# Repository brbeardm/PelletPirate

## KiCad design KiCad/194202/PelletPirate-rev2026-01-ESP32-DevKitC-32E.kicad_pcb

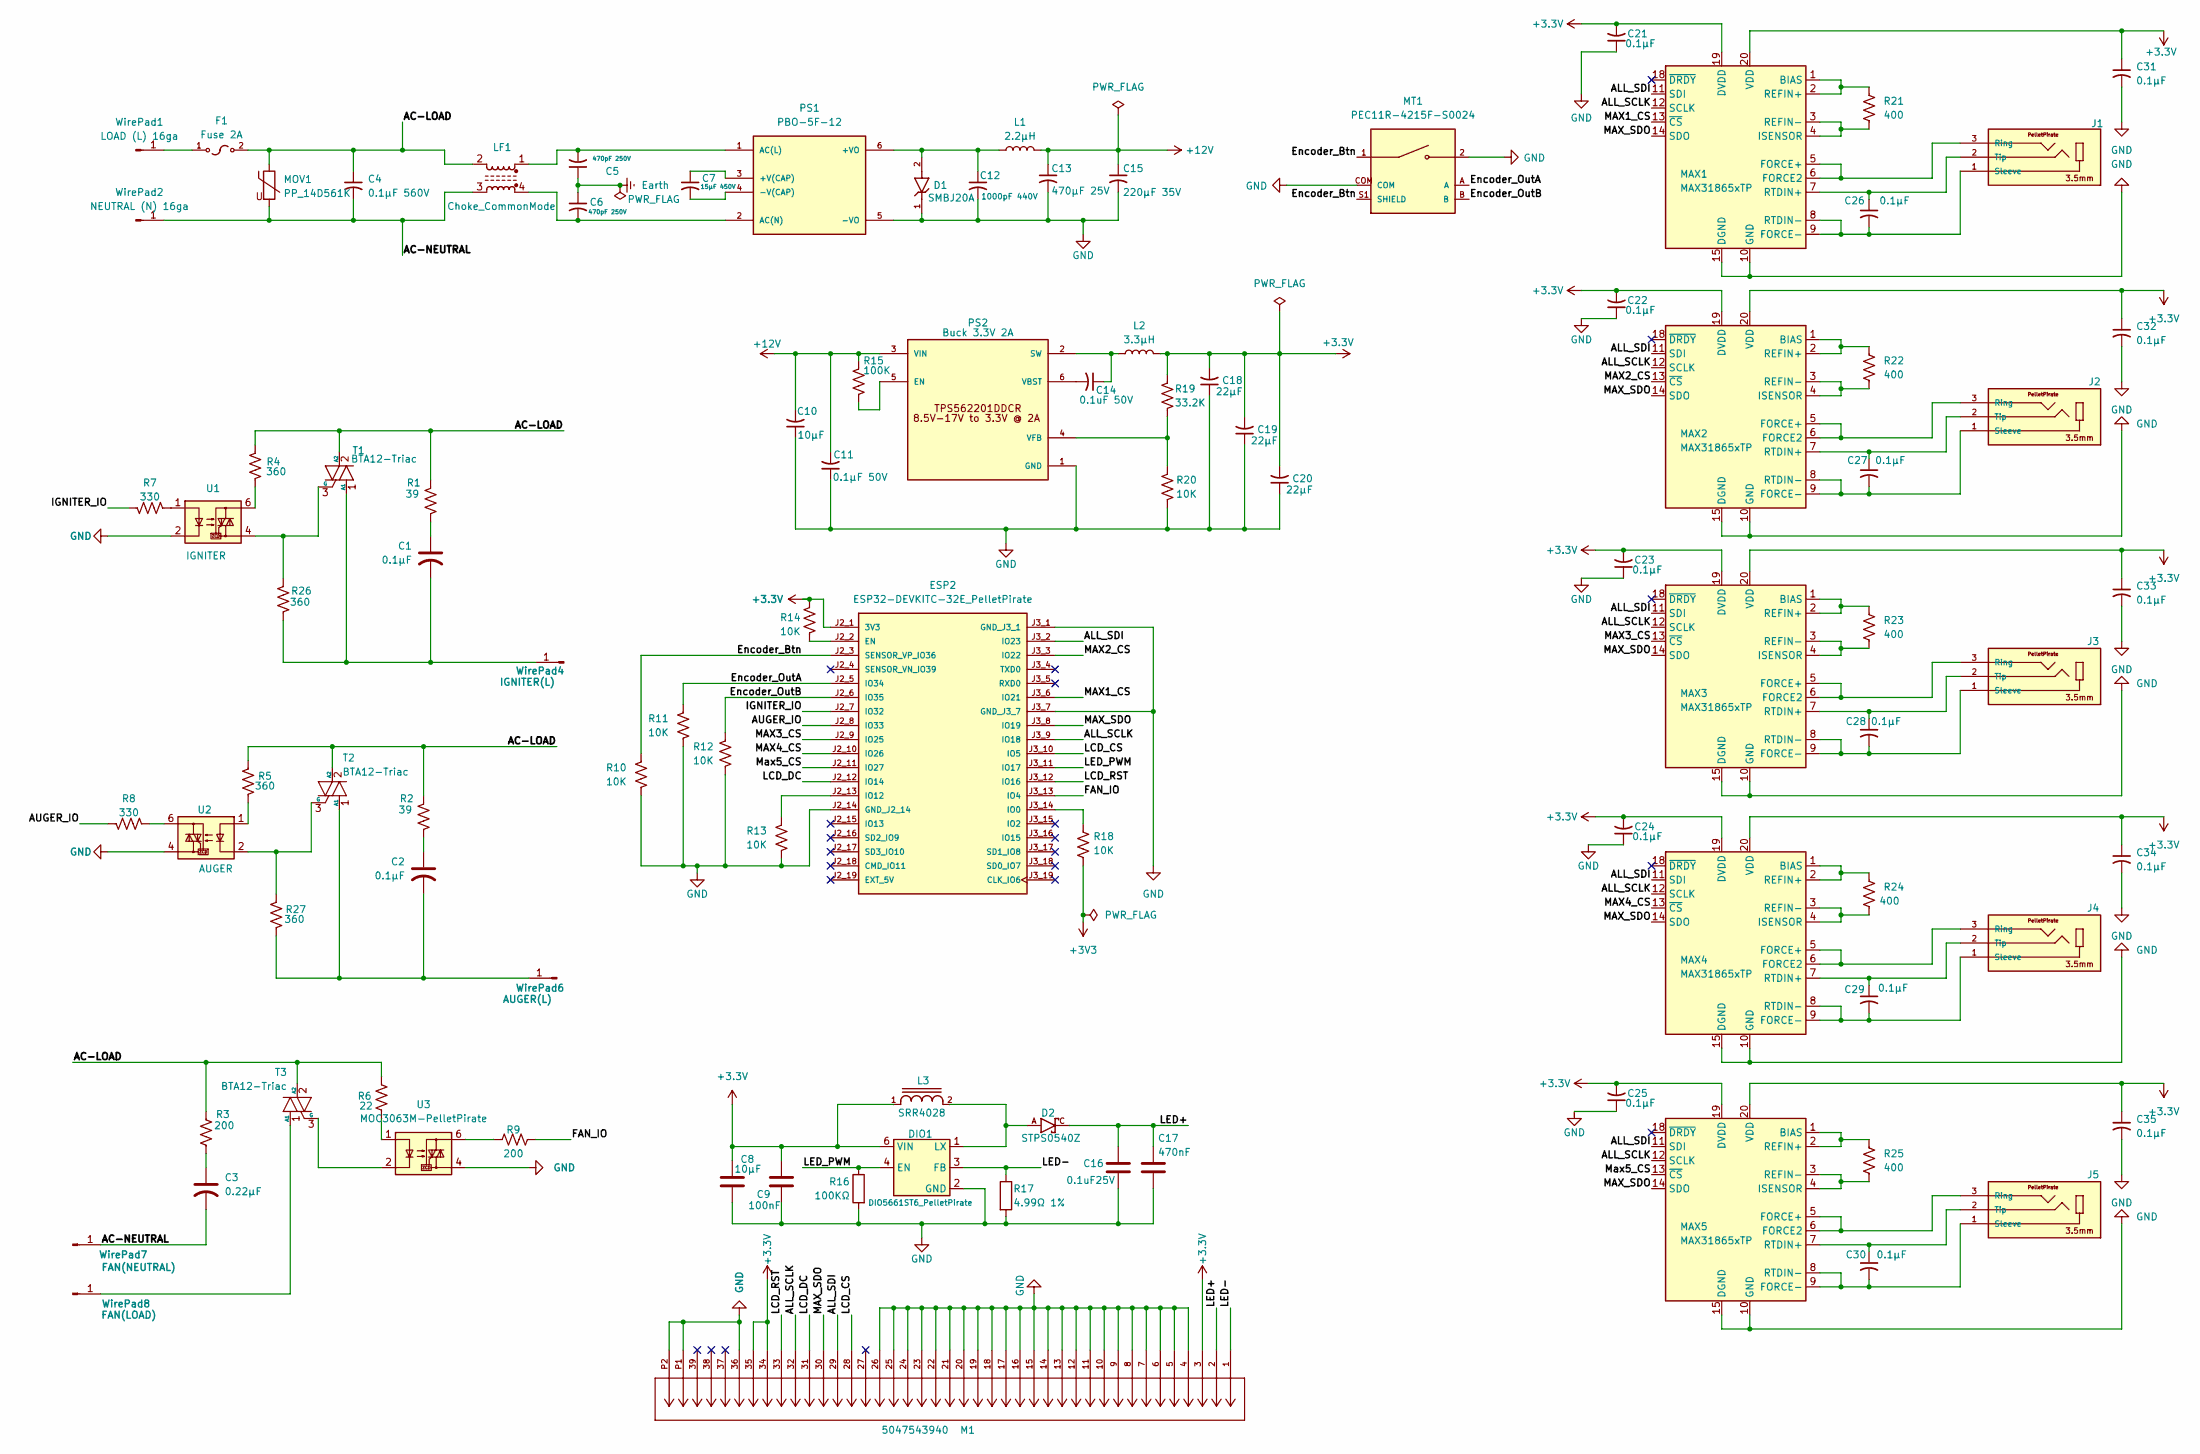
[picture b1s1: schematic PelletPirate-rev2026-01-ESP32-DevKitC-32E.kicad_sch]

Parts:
C1, C2, C21, C22, C23, C24, C25, C26, C27, C28, C29, C30, C31, C32, C33, C34, C35: 0.1µF; C_0805_2012Metric_Pad1.18x1.45mm_HandSolder
C3: 0.22µF; C_0805_2012Metric_Pad1.18x1.45mm_HandSolder
C4: 0.1µF 560V; CAPRR1500W80L1800T500H1050
C5, C6: 470pF 250V; C_Disc_D7.5mm_W5.0mm_P7.50mm
C7: 15µF 450V; CP_Radial_D10.0mm_P5.00mm
C8: 10µF; C_0603_1608Metric_Pad1.08x0.95mm_HandSolder
C9: 100nF; C_0603_1608Metric_Pad1.08x0.95mm_HandSolder
C10: 10µF; C_1206_3216Metric_Pad1.33x1.80mm_HandSolder
C11: 0.1µF 50V; C_0805_2012Metric_Pad1.18x1.45mm_HandSolder
C12: 1000pF 440V; C_Disc_D7.5mm_W5.0mm_P7.50mm
C13: 470µF 25V; CP_Radial_D10.0mm_P5.00mm
C14: 0.1uF 50V; C_0805_2012Metric_Pad1.18x1.45mm_HandSolder
C15: 220µF 35V; CP_Radial_D8.0mm_P3.50mm
C16: 0.1uF25V; C_0805_2012Metric_Pad1.18x1.45mm_HandSolder
C17: 470nF; C_0805_2012Metric_Pad1.18x1.45mm_HandSolder
C18, C19, C20: 22µF; C_1206_3216Metric_Pad1.33x1.80mm_HandSolder
D1: SMBJ20A; DIOM5436X261N_PelletPirate; PARTREV JC.07/04/25 v4; DigiKey_Part_Number SMBJ20ALFCT-ND
D2: STPS0540Z; SOD-123
DIO1: DIO5661ST6_PelletPirate; SOT-23-6
ESP2: ESP32-DEVKITC-32E_PelletPirate; MODULE_ESP32-DEVKITC-32E_PelletPirate; PARTREV 1.4
F1: Fuse 2A; SCHURTER_0031.8201; DigiKey_Part_Number 486-1258-ND
J1, J2, J3, J4, J5: SJ1-3523NG_Jack_PP; CUI_SJ1-3523NG_PelletPirate; PARTREV 1.01
L1: 2.2µH; L_2512_6332Metric
L2: 3.3µH; L_2512_6332Metric
L3: SRR4028
LF1: Choke_CommonMode; Kemet_Choke_SSRH7H_M05408
M1: 5047543940; CON_5047543940_MOL; MANUFACTURER_PART_NUMBER 5047543940
MAX1, MAX2, MAX3, MAX4, MAX5: MAX31865xTP; TQFN-20-1EP_5x5mm_P0.65mm_EP3.25x3.25mm
MOV1: PP_14D561K; Varistor_14mm_p7.5mm
MT1: PEC11R-4215F-S0024; XDCR_PEC11R-4215F-S0024; PARTREV Rev. 09/19; DigiKey_Part_Number PEC11R-4215F-S0024-ND
PS1: PBO-5F-12; PBO-5F-12_pp2; PARTREV 1.0
PS2: Buck 3.3V 2A; SOT95P280X110-6N; PARTREV A
R1, R2: 39; C_0805_2012Metric_Pad1.18x1.45mm_HandSolder
R3, R9: 200; C_0805_2012Metric_Pad1.18x1.45mm_HandSolder
R4, R5, R26, R27: 360; C_0805_2012Metric_Pad1.18x1.45mm_HandSolder
R6: 22; C_0805_2012Metric_Pad1.18x1.45mm_HandSolder
R7, R8: 330; C_0805_2012Metric_Pad1.18x1.45mm_HandSolder
R10, R11, R12, R13, R14, R18, R20: 10K; C_0805_2012Metric_Pad1.18x1.45mm_HandSolder
R15: 100K; C_0805_2012Metric_Pad1.18x1.45mm_HandSolder
R16: 100KΩ; R_0603_1608Metric_Pad0.98x0.95mm_HandSolder
R17: 4.99Ω 1%; R_1206_3216Metric_Pad1.30x1.75mm_HandSolder
R19: 33.2K; C_0805_2012Metric_Pad1.18x1.45mm_HandSolder
R21, R22, R23, R24, R25: 400; C_0805_2012Metric_Pad1.18x1.45mm_HandSolder
T1, T2, T3: BTA12-Triac; TO-220-3_Vertical
U1: IGNITER; MOC3063M-PP2
U2: AUGER; MOC3063M-PP2
U3: MOC3063M-PelletPirate; MOC3063M-PP2
WirePad1: LOAD (L) 16ga; SolderWire-1.5sqmm_1x01_D1.7mm_OD3mm
WirePad2: NEUTRAL (N) 16ga; SolderWire-1.5sqmm_1x01_D1.7mm_OD3mm
WirePad4: IGNITER(L); SolderWire-1.5sqmm_1x01_D1.7mm_OD3mm
WirePad6: AUGER(L); SolderWire-1.5sqmm_1x01_D1.7mm_OD3mm
WirePad7: FAN(NEUTRAL); SolderWire-1.5sqmm_1x01_D1.7mm_OD3mm
WirePad8: FAN(LOAD); SolderWire-1.5sqmm_1x01_D1.7mm_OD3mm

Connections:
+3.3V: C8.1, C9.1, C18.2, C19.2, C20.2, C21.2, C22.2, C23.2, C24.2, C25.2, C31.1, C32.1, C33.1, C34.1, C35.1, DIO1.6 (VIN), ESP2.J2_1 (3V3), L2.2, L3.1, M1.3, M1.34, M1.35, MAX1.19 (DVDD), MAX1.20 (VDD), MAX2.19 (DVDD), MAX2.20 (VDD), MAX3.19 (DVDD), MAX3.20 (VDD), MAX4.19 (DVDD), MAX4.20 (VDD), MAX5.19 (DVDD), MAX5.20 (VDD), R14.1, R19.1
+3V3: R18.2
+12V: C10.2, C11.2, C13.1, C15.1, L1.2, PS2.3 (VIN), R15.1
/AC-LOAD: C4.1, F1.2, LF1.2, MOV1.1, R1.1, R2.1, R3.1, R4.1, R5.1, R6.1, T1.2 (A2), T2.2 (A2), T3.2 (A2)
/AC-NEUTRAL: C3.2, C4.2, LF1.3, MOV1.2, WirePad2.1 (Pin_1_1), WirePad7.1 (Pin_1_1); also elsewhere on the board
/ALL_SCLK: ESP2.J3_9 (IO18), M1.32, MAX1.12 (SCLK), MAX2.12 (SCLK), MAX3.12 (SCLK), MAX4.12 (SCLK), MAX5.12 (SCLK)
/ALL_SDI: ESP2.J3_2 (IO23), M1.29, MAX1.11 (SDI), MAX2.11 (SDI), MAX3.11 (SDI), MAX4.11 (SDI), MAX5.11 (SDI)
/AUGER_IO: ESP2.J2_8 (IO33), R8.2
/Encoder_Btn: ESP2.J2_3 (SENSOR_VP_IO36), MT1.1, MT1.S1 (SHIELD), MT1.S2 (SHIELD), R10.1
/Encoder_OutA: ESP2.J2_5 (IO34), MT1.A, R11.1
/Encoder_OutB: ESP2.J2_6 (IO35), MT1.B, R12.1
/FAN_IO: ESP2.J3_13 (IO4), R9.2
/IGNITER_IO: ESP2.J2_7 (IO32), R7.2
/LCD_CS: ESP2.J3_10 (IO5), M1.28
/LCD_DC: ESP2.J2_12 (IO14), M1.31
/LCD_RST: ESP2.J3_12 (IO16), M1.33
/LED+: C16.1, C17.1, D2.C, M1.2
/LED-: DIO1.3 (FB), M1.1, R17.1
/LED_PWM: DIO1.4 (EN), ESP2.J3_11 (IO17), R16.1
/MAX1_CS: ESP2.J3_6 (IO21), MAX1.13 (~CS)
/MAX2_CS: ESP2.J3_3 (IO22), MAX2.13 (~CS)
/MAX3_CS: ESP2.J2_9 (IO25), MAX3.13 (~CS)
/MAX4_CS: ESP2.J2_10 (IO26), MAX4.13 (~CS)
/MAX_SDO: ESP2.J3_8 (IO19), M1.30, MAX1.14 (SDO), MAX2.14 (SDO), MAX3.14 (SDO), MAX4.14 (SDO), MAX5.14 (SDO)
/Max5_CS: ESP2.J2_11 (IO27), MAX5.13 (~CS)
Earth: C5.1, C6.1
GND: C8.2, C9.2, C10.1, C11.1, C12.2, C13.2, C15.2, C16.2, C17.2, C18.1, C19.1, C20.1, C21.1, C22.1, C23.1, C24.1, C25.1, C31.2, C32.2, C33.2, C34.2, C35.2, D1.1, DIO1.2 (GND), ESP2.J2_14 (GND_J2_14), ESP2.J3_1 (GND_J3_1), ESP2.J3_7 (GND_J3_7), M1.4, M1.5, M1.6, M1.7, M1.8, M1.9, M1.10, M1.11, M1.12, M1.13, M1.14, M1.15, M1.16, M1.17, M1.18, M1.19, M1.20, M1.21, M1.22, M1.23, M1.24, M1.25, M1.26, M1.36, M1.P1, M1.P2, MAX1.10 (GND), MAX1.15 (DGND), MAX1.16 (GND), MAX1.21 (GND), MAX2.10 (GND), MAX2.15 (DGND), MAX2.16 (GND), MAX2.21 (GND), MAX3.10 (GND), MAX3.15 (DGND), MAX3.16 (GND), MAX3.21 (GND), MAX4.10 (GND), MAX4.15 (DGND), MAX4.16 (GND), MAX4.21 (GND), MAX5.10 (GND), MAX5.15 (DGND), MAX5.16 (GND), MAX5.21 (GND), MT1.2, MT1.COM, PS1.5 (-VO), PS2.1 (GND), R10.2, R11.2, R12.2, R13.2, R16.2, R17.2, R20.2, U1.2, U2.4, U3.4
unnamed: C1.1, R1.2
unnamed: C2.1, R2.2
unnamed: C3.1, R3.2
unnamed: D2.A, DIO1.1 (LX), L3.2
unnamed: ESP2.J2_2 (EN), R14.2
unnamed: ESP2.J3_14 (IO0), R18.1
unnamed: ESP2.J2_13 (IO12), R13.1
unnamed: J1.3 (Ring), MAX1.5 (FORCE+), MAX1.6 (FORCE2)
unnamed: C26.2, J1.1 (Sleeve), MAX1.8 (RTDIN-), MAX1.9 (FORCE-)
unnamed: C26.1, J1.2 (Tip), MAX1.7 (RTDIN+)
unnamed: J2.3 (Ring), MAX2.5 (FORCE+), MAX2.6 (FORCE2)
unnamed: C27.2, J2.1 (Sleeve), MAX2.8 (RTDIN-), MAX2.9 (FORCE-)
unnamed: C27.1, J2.2 (Tip), MAX2.7 (RTDIN+)
unnamed: J3.3 (Ring), MAX3.5 (FORCE+), MAX3.6 (FORCE2)
unnamed: C28.2, J3.1 (Sleeve), MAX3.8 (RTDIN-), MAX3.9 (FORCE-)
unnamed: C28.1, J3.2 (Tip), MAX3.7 (RTDIN+)
unnamed: J4.3 (Ring), MAX4.5 (FORCE+), MAX4.6 (FORCE2)
unnamed: C29.2, J4.1 (Sleeve), MAX4.8 (RTDIN-), MAX4.9 (FORCE-)
unnamed: C29.1, J4.2 (Tip), MAX4.7 (RTDIN+)
unnamed: J5.3 (Ring), MAX5.5 (FORCE+), MAX5.6 (FORCE2)
unnamed: C30.2, J5.1 (Sleeve), MAX5.8 (RTDIN-), MAX5.9 (FORCE-)
unnamed: C30.1, J5.2 (Tip), MAX5.7 (RTDIN+)
unnamed: MAX1.1 (BIAS), MAX1.2 (REFIN+), R21.1
unnamed: MAX1.3 (REFIN-), MAX1.4 (ISENSOR), R21.2
unnamed: MAX2.1 (BIAS), MAX2.2 (REFIN+), R22.1
unnamed: MAX2.3 (REFIN-), MAX2.4 (ISENSOR), R22.2
unnamed: MAX3.1 (BIAS), MAX3.2 (REFIN+), R23.1
unnamed: MAX3.3 (REFIN-), MAX3.4 (ISENSOR), R23.2
unnamed: MAX4.1 (BIAS), MAX4.2 (REFIN+), R24.1
unnamed: MAX4.3 (REFIN-), MAX4.4 (ISENSOR), R24.2
unnamed: MAX5.1 (BIAS), MAX5.2 (REFIN+), R25.1
unnamed: MAX5.3 (REFIN-), MAX5.4 (ISENSOR), R25.2
unnamed: C7.1, PS1.3 (+V(CAP))
unnamed: C12.1, D1.2, L1.1, PS1.6 (+VO)
unnamed: C7.2, PS1.4 (-V(CAP))
unnamed: C5.2, LF1.1, PS1.1 (AC(L))
unnamed: C6.2, LF1.4, PS1.2 (AC(N))
unnamed: PS2.5 (EN), R15.2
unnamed: C14.1, L2.1, PS2.2 (SW)
unnamed: C14.2, PS2.6 (VBST)
unnamed: PS2.4 (VFB), R19.2, R20.1
unnamed: R4.2, U1.6
unnamed: R5.2, U2.1
unnamed: R6.2, U3.1
unnamed: R7.1, U1.1
unnamed: R8.1, U2.6
unnamed: R9.1, U3.6
unnamed: C1.2, R26.2, T1.1 (A1), WirePad4.1 (Pin_1_1)
unnamed: R26.1, T1.3 (G), U1.4
unnamed: C2.2, R27.2, T2.1 (A1), WirePad6.1 (Pin_1_1)
unnamed: R27.1, T2.3 (G), U2.2
unnamed: T3.1 (A1), WirePad8.1 (Pin_1_1)
unnamed: T3.3 (G), U3.2
unnamed: F1.1, WirePad1.1 (Pin_1_1)

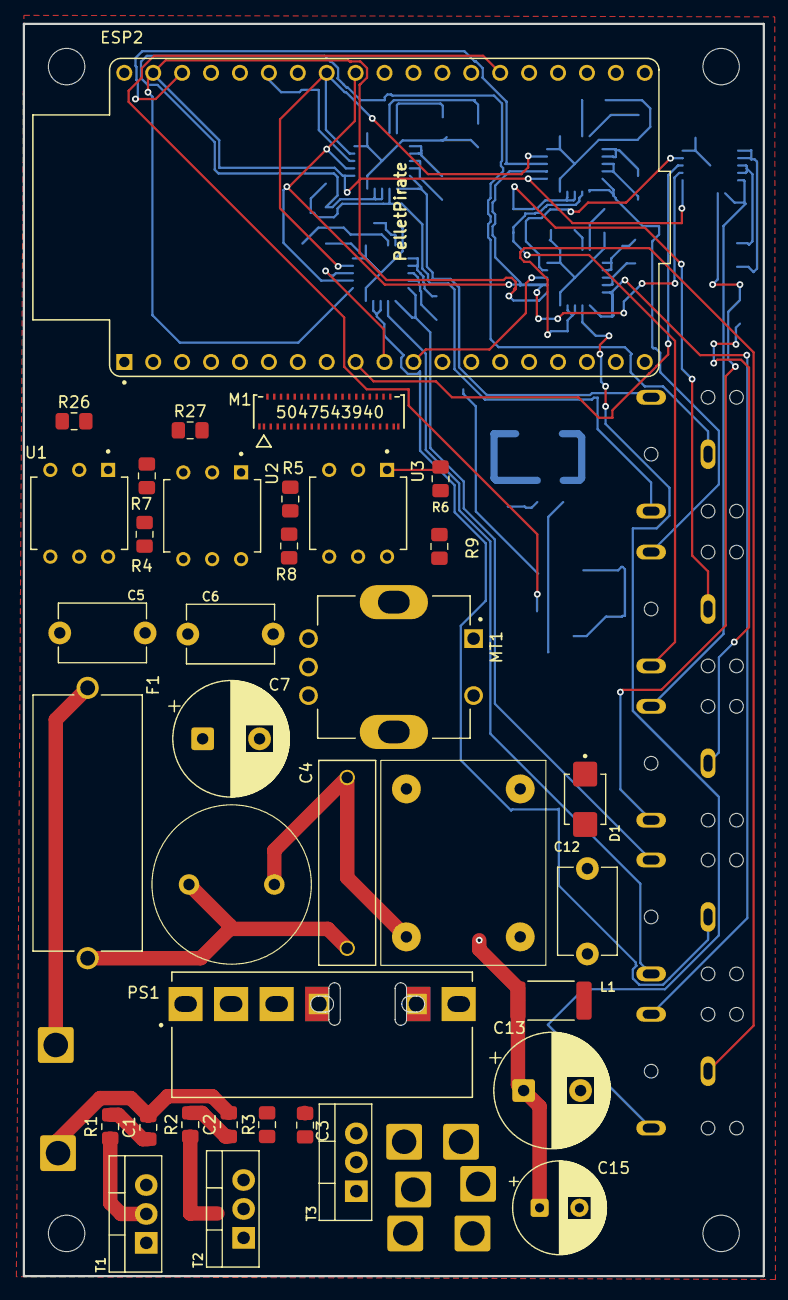
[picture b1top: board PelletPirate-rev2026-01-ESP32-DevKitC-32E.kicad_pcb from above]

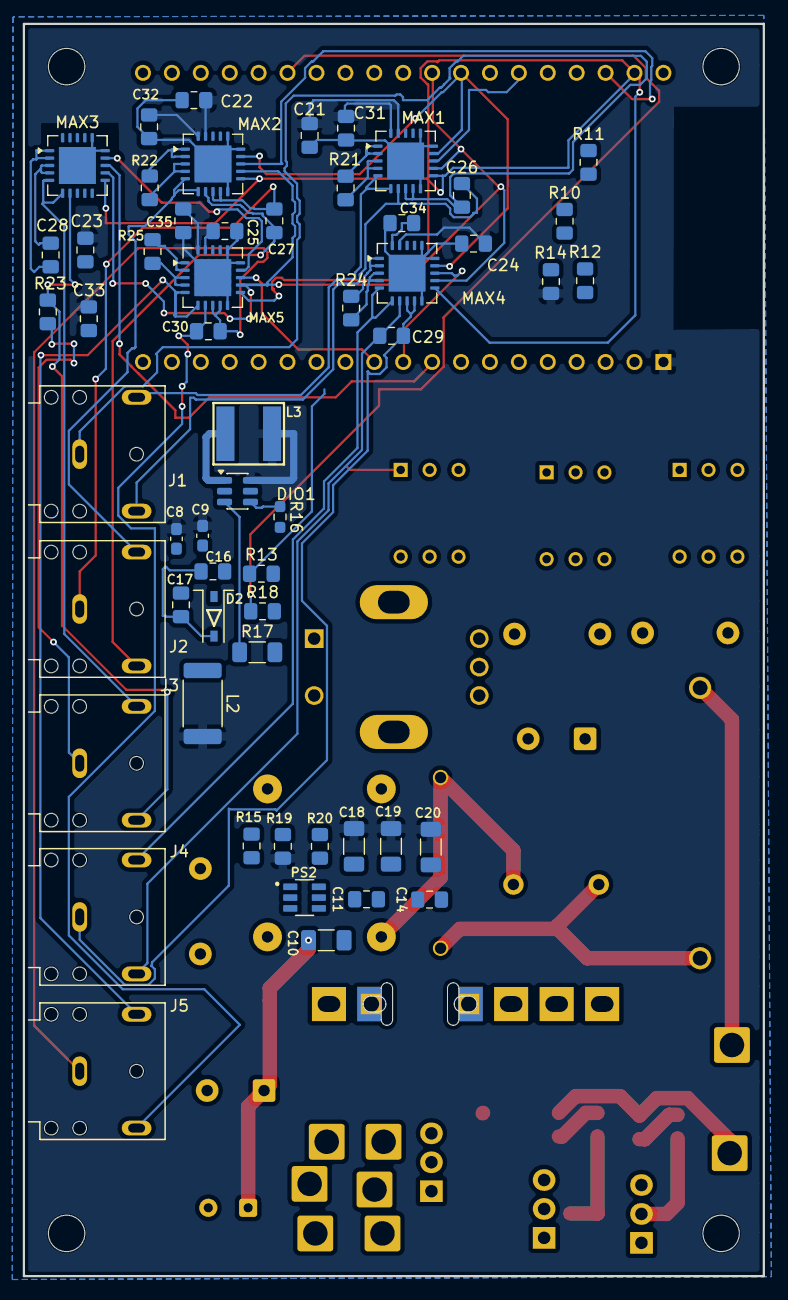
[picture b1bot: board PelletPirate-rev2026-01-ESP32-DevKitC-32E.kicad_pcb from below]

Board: 2 copper layers, 65.0 x 110.0 mm, 100 parts (56 on the bottom side), 80 nets.

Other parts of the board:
WirePad3: IGNITER(NEUTRAL); SolderWire-1.5sqmm_1x01_D1.7mm_OD3mm
WirePad5: AUGER(NEUTRAL); SolderWire-1.5sqmm_1x01_D1.7mm_OD3mm

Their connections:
/AC-NEUTRAL: WirePad3.1 (Pin_1_1), WirePad5.1 (Pin_1_1); also elsewhere on the board

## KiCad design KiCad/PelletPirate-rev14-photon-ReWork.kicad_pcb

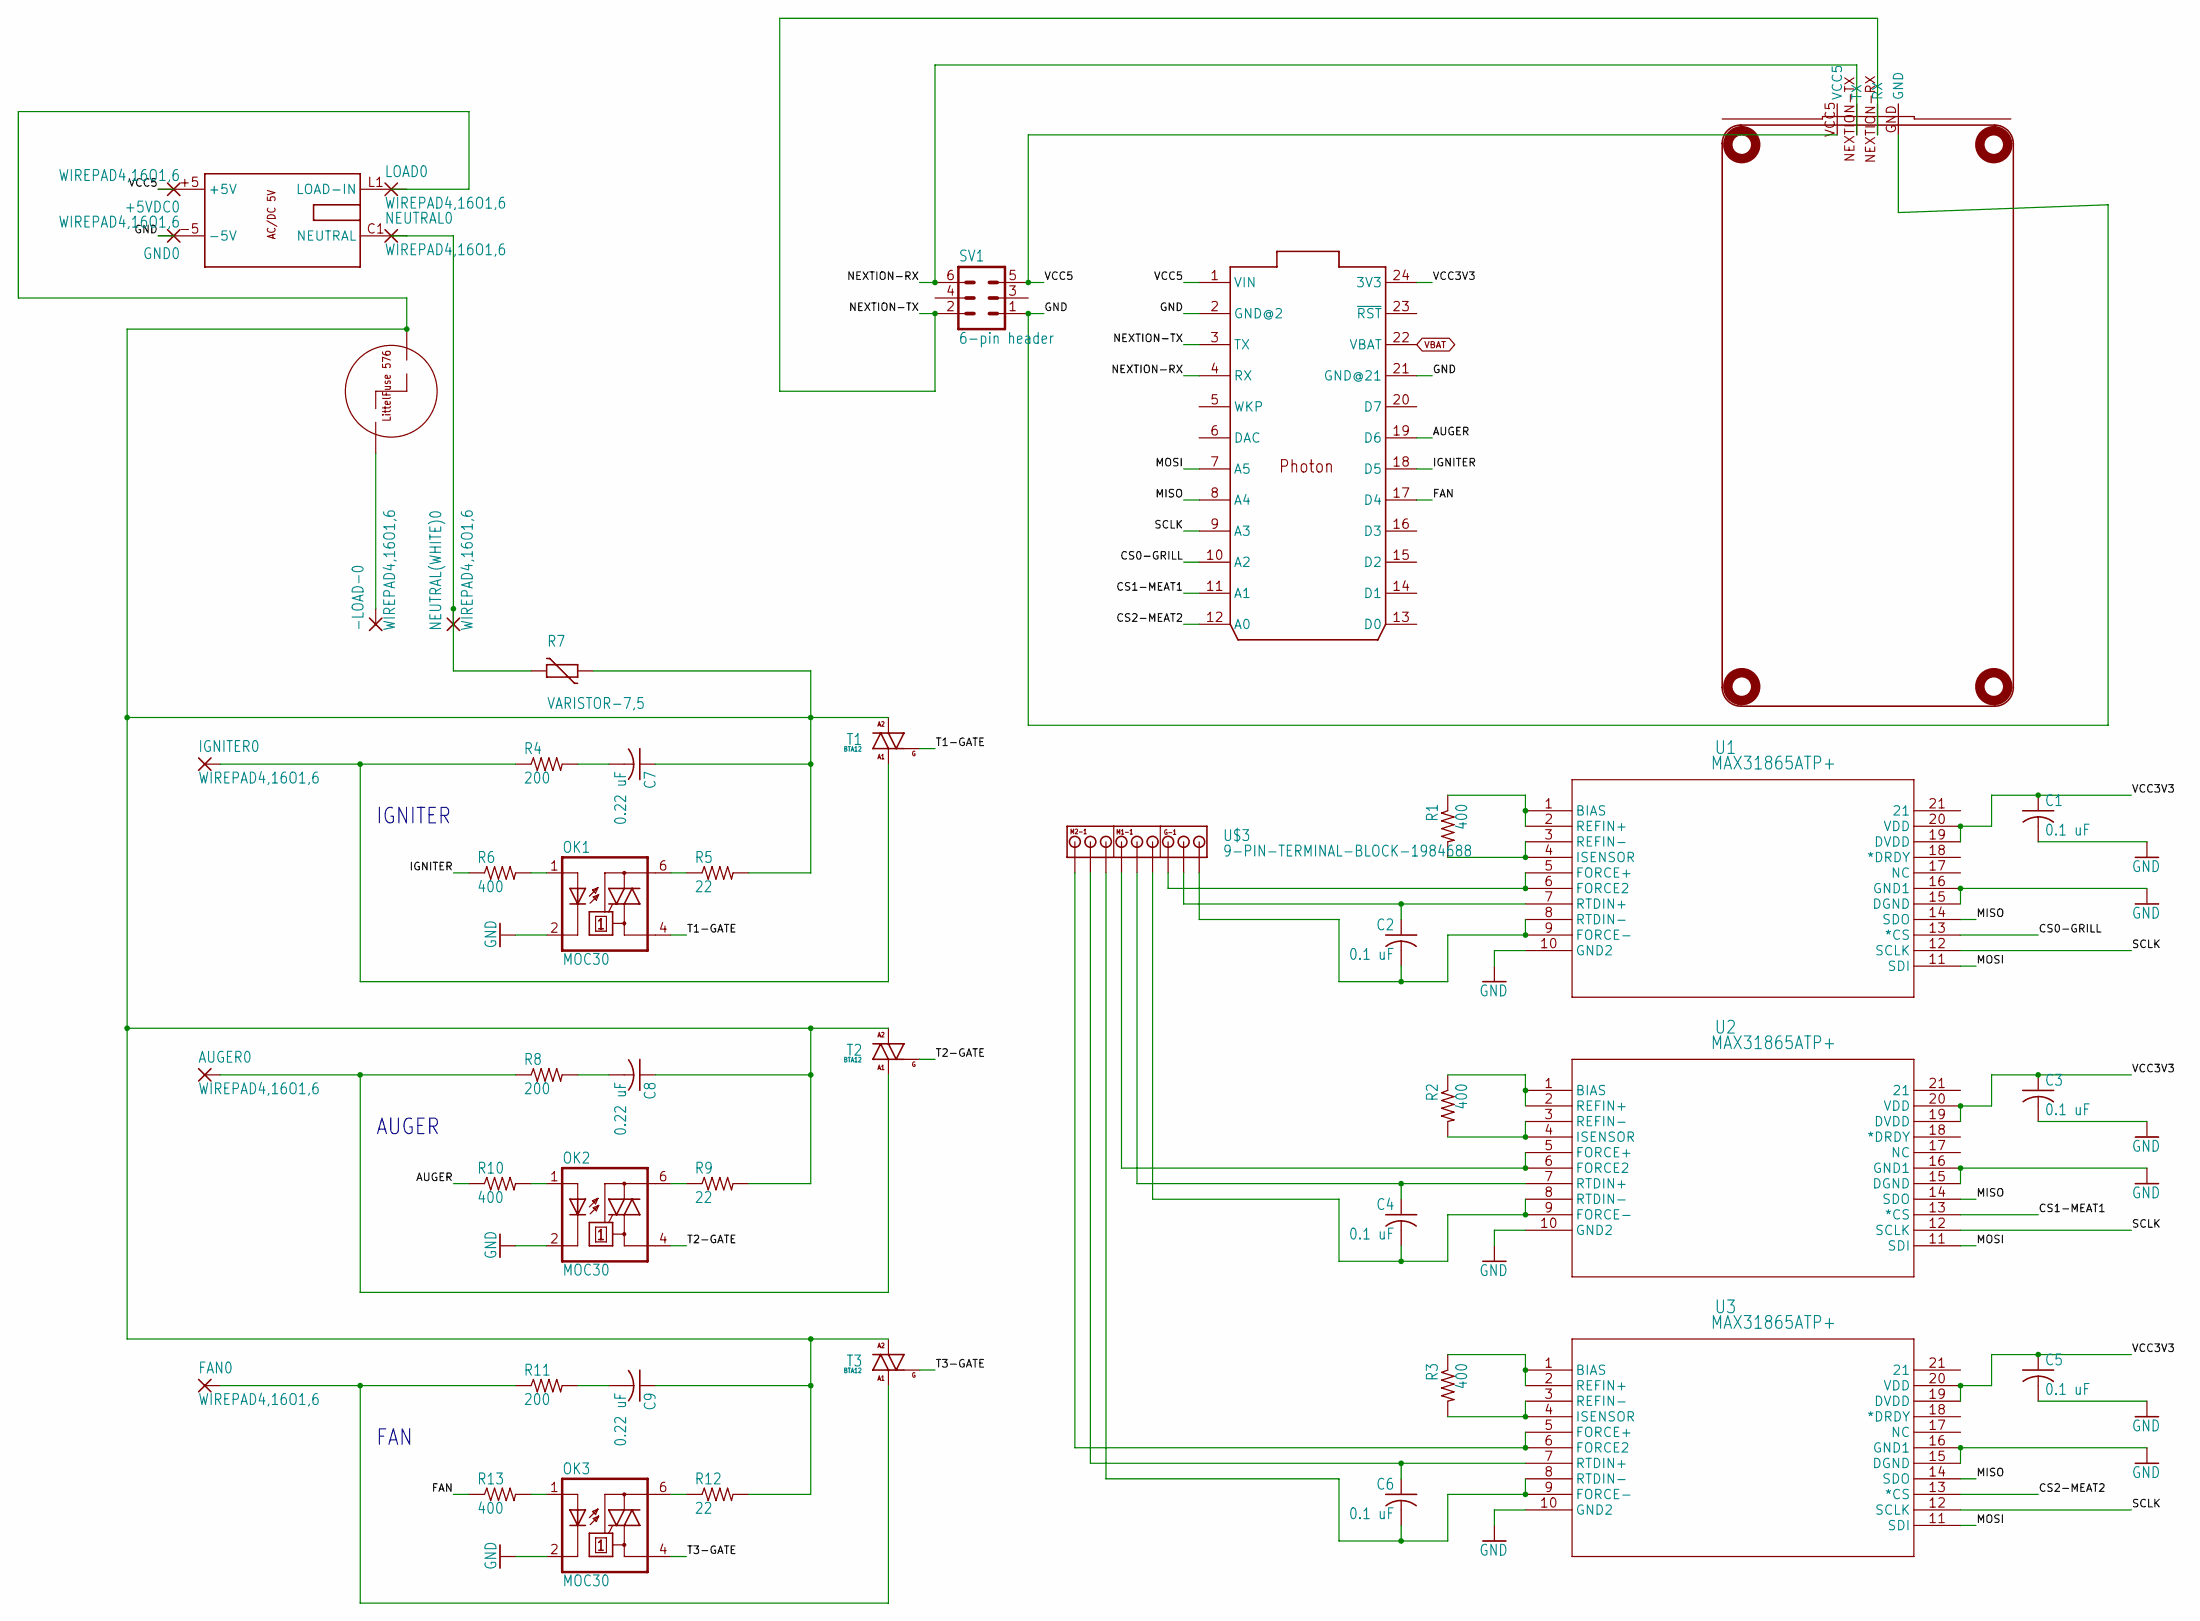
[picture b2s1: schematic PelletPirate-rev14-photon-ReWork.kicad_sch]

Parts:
+5VDC0: WIREPAD4,16O1,6; 4,16O1,6
-LOAD-0: WIREPAD4,16O1,6; 4,16O1,6
AUGER0: WIREPAD4,16O1,6; 4,16O1,6
C1, C2, C3, C4, C5, C6: 0.1 uF; C1812
C7, C8, C9: 0.22 uF; C1812
FAN0: WIREPAD4,16O1,6; 4,16O1,6
GND0: WIREPAD4,16O1,6; 4,16O1,6
IGNITER0: WIREPAD4,16O1,6; 4,16O1,6
LOAD0: WIREPAD4,16O1,6; 4,16O1,6
NEUTRAL0: WIREPAD4,16O1,6; 4,16O1,6
NEUTRAL(WHITE)0: WIREPAD4,16O1,6; 4,16O1,6
OK1, OK2, OK3: MOC30; DIL06
R1, R2, R3, R6, R10, R13: 400; R2010
R4, R8, R11: 200; R2010
R5, R9, R12: 22; R2010
R7: VARISTOR-7,5; R-7,5
SV1: 6-pin header; MA03-2
T1, T2, T3: BTA12; TO-220AB-INSULATED(BTA12)
U1, U2, U3: MAX31865ATP+; 21-0140L_T2055-5
U$1: ACDC-5VTHROUGH-HOLD; ACDC-5V
U$2: LITTELFUSE-576
U$3: 9-PIN-TERMINAL-BLOCK-1984688; PHOENIX-9PIN-651-1984688
U$4: PHOTON_WITH_HEADERS; PHOTON
U$5: NEXTION-DISPLAY; NEXTION_NX4024K032

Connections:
AUGER: R10.1, U$4.19 (D6)
CS0-GRILL: U1.13 (*CS), U$4.10 (A2)
CS1-MEAT1: U2.13 (*CS), U$4.11 (A1)
CS2-MEAT2: U3.13 (*CS), U$4.12 (A0)
FAN: R13.1, U$4.17 (D4)
GND: C1.2, C3.2, C5.2, GND0.1, OK1.2 (C), OK2.2 (C), OK3.2 (C), SV1.1, U1.10 (GND2), U1.15 (DGND), U1.16 (GND1), U2.10 (GND2), U2.15 (DGND), U2.16 (GND1), U3.10 (GND2), U3.15 (DGND), U3.16 (GND1), U$1.-5 (-5V), U$4.2 (GND@2), U$4.21 (GND@21), U$5.GND
GRILLBIASREFIN+: R1.1, U1.1 (BIAS), U1.2 (REFIN+)
GRILLFORCE+FORCE2: U1.5 (FORCE+), U1.6 (FORCE2), U$3.GRILL-1
GRILLREFIN-ISENSOR: R1.2, U1.3 (REFIN-), U1.4 (ISENSOR)
GRILLRTDIN+: C2.1, U1.7 (RTDIN+), U$3.GRILL-2
GRILLRTDIN-FORCE-: C2.2, U1.8 (RTDIN-), U1.9 (FORCE-), U$3.GRILL-3
IGNITER: R6.1, U$4.18 (D5)
MEAT1BIASREFIN+: R2.1, U2.1 (BIAS), U2.2 (REFIN+)
MEAT1FORCE+FORCE2: U2.5 (FORCE+), U2.6 (FORCE2), U$3.MEAT1-1
MEAT1REFIN-ISENSOR: R2.2, U2.3 (REFIN-), U2.4 (ISENSOR)
MEAT1RTDIN+: C4.1, U2.7 (RTDIN+), U$3.MEAT1-2
MEAT1RTDIN-FORCE-: C4.2, U2.8 (RTDIN-), U2.9 (FORCE-), U$3.MEAT1-3
MEAT2BIASREFIN+: R3.1, U3.1 (BIAS), U3.2 (REFIN+)
MEAT2FORCE+FORCE2: U3.5 (FORCE+), U3.6 (FORCE2), U$3.MEAT2-1
MEAT2REFIN-ISENSOR: R3.2, U3.3 (REFIN-), U3.4 (ISENSOR)
MEAT2RTDIN+: C6.1, U3.7 (RTDIN+), U$3.MEAT2-2
MEAT2RTDIN-FORCE-: C6.2, U3.8 (RTDIN-), U3.9 (FORCE-), U$3.MEAT2-3
MISO: U1.14 (SDO), U2.14 (SDO), U3.14 (SDO), U$4.8 (A4)
MOSI: U1.11 (SDI), U2.11 (SDI), U3.11 (SDI), U$4.7 (A5)
unnamed: OK1.6 (A2), R5.1
unnamed: OK1.1 (A), R6.2
unnamed: -LOAD-0.1, U$2.P$1
unnamed: C7.1, C8.1, C9.1, LOAD0.1, R5.2, R7.1, R9.2, R12.2, T1.A2, T2.A2, T3.A2, U$1.L1 (LOAD-IN), U$2.P$2
unnamed: NEUTRAL0.1, NEUTRAL(WHITE)0.1, R7.2, U$1.C1 (NEUTRAL)
unnamed: IGNITER0.1, R4.1, T1.A1
unnamed: C7.2, R4.2
unnamed: OK2.1 (A), R10.2
unnamed: C8.2, R8.2
unnamed: AUGER0.1, R8.1, T2.A1
unnamed: OK2.6 (A2), R9.1
unnamed: OK3.1 (A), R13.2
unnamed: C9.2, R11.2
unnamed: FAN0.1, R11.1, T3.A1
unnamed: OK3.6 (A2), R12.1
NEXTION-RX: SV1.6, U$4.4 (RX), U$5.NEXTION-TX (TX)
NEXTION-TX: SV1.2, U$4.3 (TX), U$5.NEXTION-RX (RX)
SCLK: U1.12 (SCLK), U2.12 (SCLK), U3.12 (SCLK), U$4.9 (A3)
T1-GATE: OK1.4 (A1), T1.G
T2-GATE: OK2.4 (A1), T2.G
T3-GATE: OK3.4 (A1), T3.G
VBAT: U$4.22 (VBAT)
VCC3V3: C1.1, C3.1, C5.1, U1.19 (DVDD), U1.20 (VDD), U2.19 (DVDD), U2.20 (VDD), U3.19 (DVDD), U3.20 (VDD), U$4.24 (3V3)
VCC5: +5VDC0.1, SV1.5, U$1.+5 (+5V), U$4.1 (VIN), U$5.VCC5

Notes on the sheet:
IGNITER
AUGER
FAN

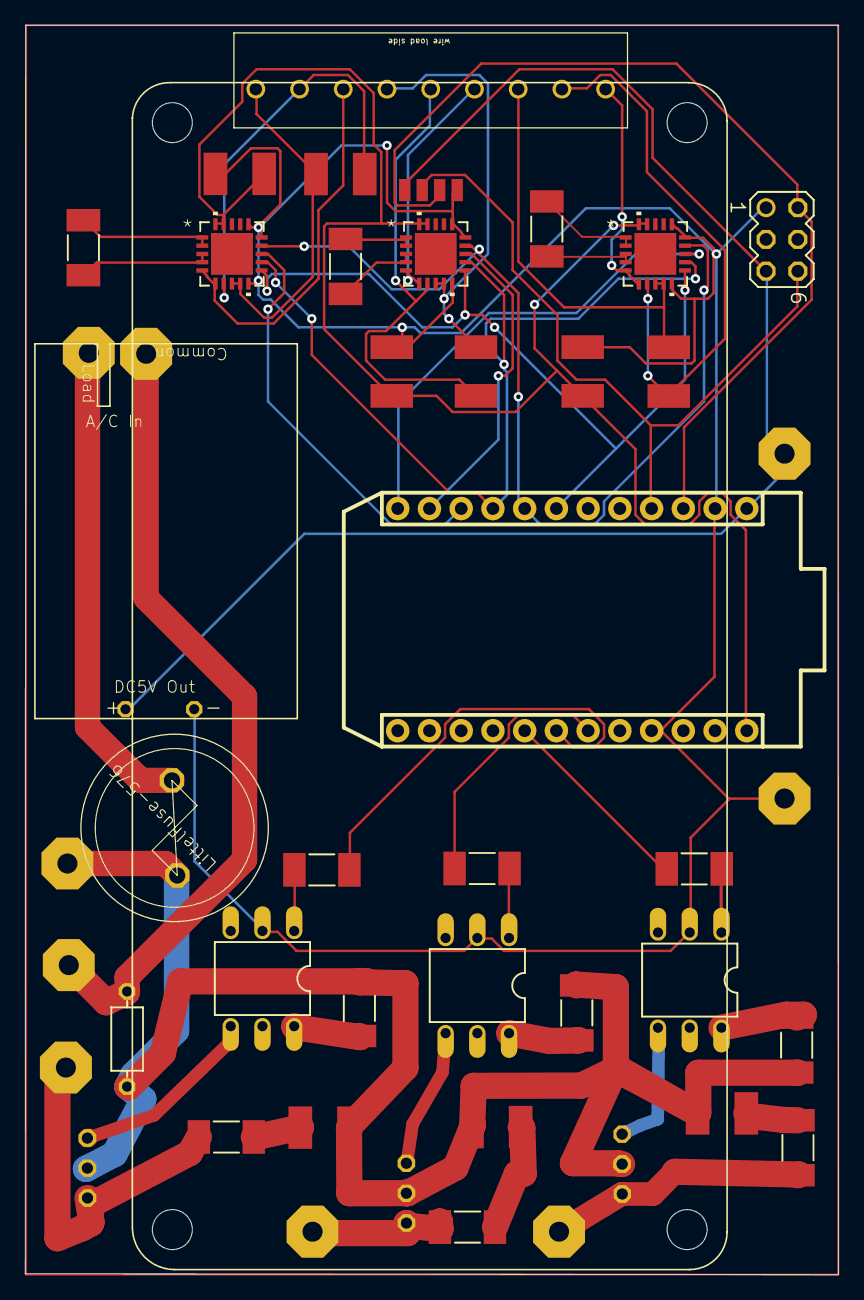
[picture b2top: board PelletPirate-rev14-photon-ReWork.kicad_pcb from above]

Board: 2 copper layers, 65.1 x 100.0 mm, 46 parts (0 on the bottom side), 47 nets.
